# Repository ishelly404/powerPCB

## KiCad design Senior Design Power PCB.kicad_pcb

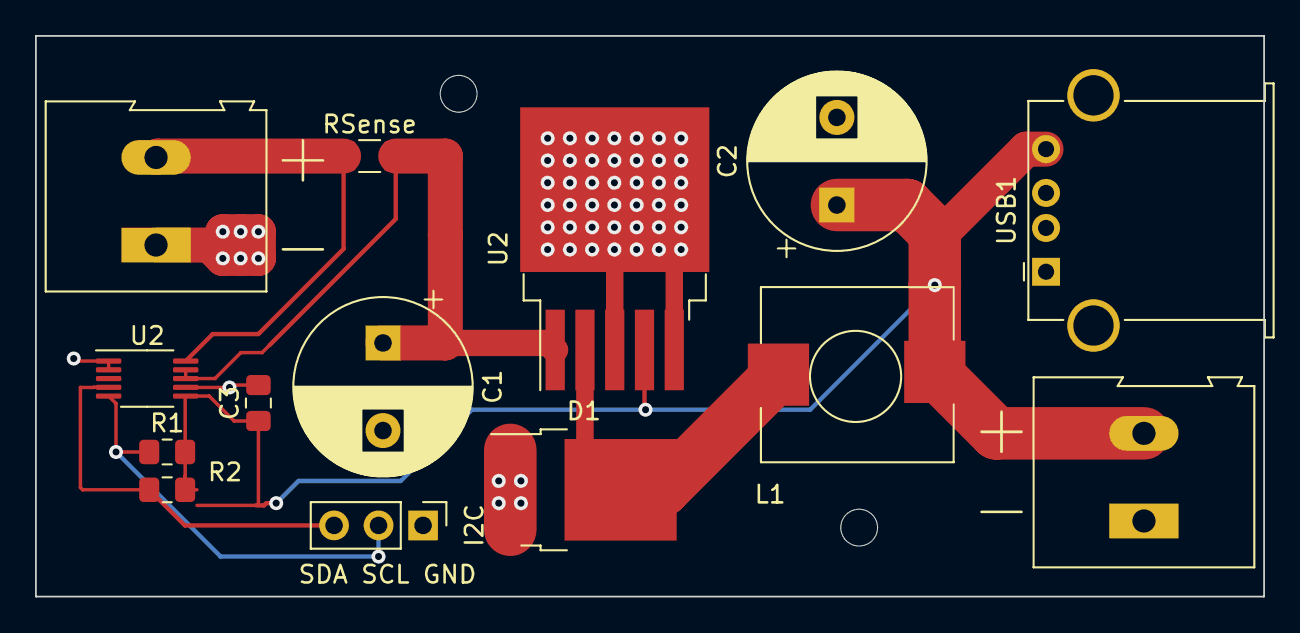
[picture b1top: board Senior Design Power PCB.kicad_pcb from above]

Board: 2 copper layers, 70.1 x 32.0 mm, 13 parts (0 on the bottom side), 5 nets.

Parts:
 : TerminalBlock_Altech_AK300-2_P5.00mm
C1, C2: CP_Radial_D10.0mm_P5.00mm
C3: C_0805_2012Metric_Pad1.15x1.40mm_HandSolder
D1: TO-252-2
I2C: PinHeader_1x03_P2.54mm_Vertical
L1: SRP1038C-330M
R1, R2: R_0805_2012Metric_Pad1.15x1.40mm_HandSolder
RSense: R_1206_3216Metric_Pad1.42x1.75mm_HandSolder
U2: VSSOP-10_3x3mm_P0.5mm
U2#2: TO-263-5_TabPin3
USB1: USB_A_Stewart_SS-52100-001_Horizontal

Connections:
5V: C2.1, C3.1, L1.2, R1.2, R2.2, U2.6, U2#2.4, USB1.4
B+: C1.1, RSense.2, U2.8, U2.9, U2#2.1
B-: .1, C2.2, C3.2, D1.1, D1.3, I2C.1, U2.1, U2.2, U2.7, U2#2.3, U2#2.5, USB1.1, USB1.5
SCL: I2C.2, R1.1, U2.5
SDA: I2C.3, R2.1, U2.4

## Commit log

2019-10-29 Initial commit, board sent for manufacturing
2019-10-31 Fixed some bugs, added screenshots
